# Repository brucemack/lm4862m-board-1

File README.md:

Overview
========

A KiCad schematic/PCB for a simple breakout board for the LM4862M 
audio amplifier.  Includes a connection for a volume control.

Schematic
=========

PCB
===

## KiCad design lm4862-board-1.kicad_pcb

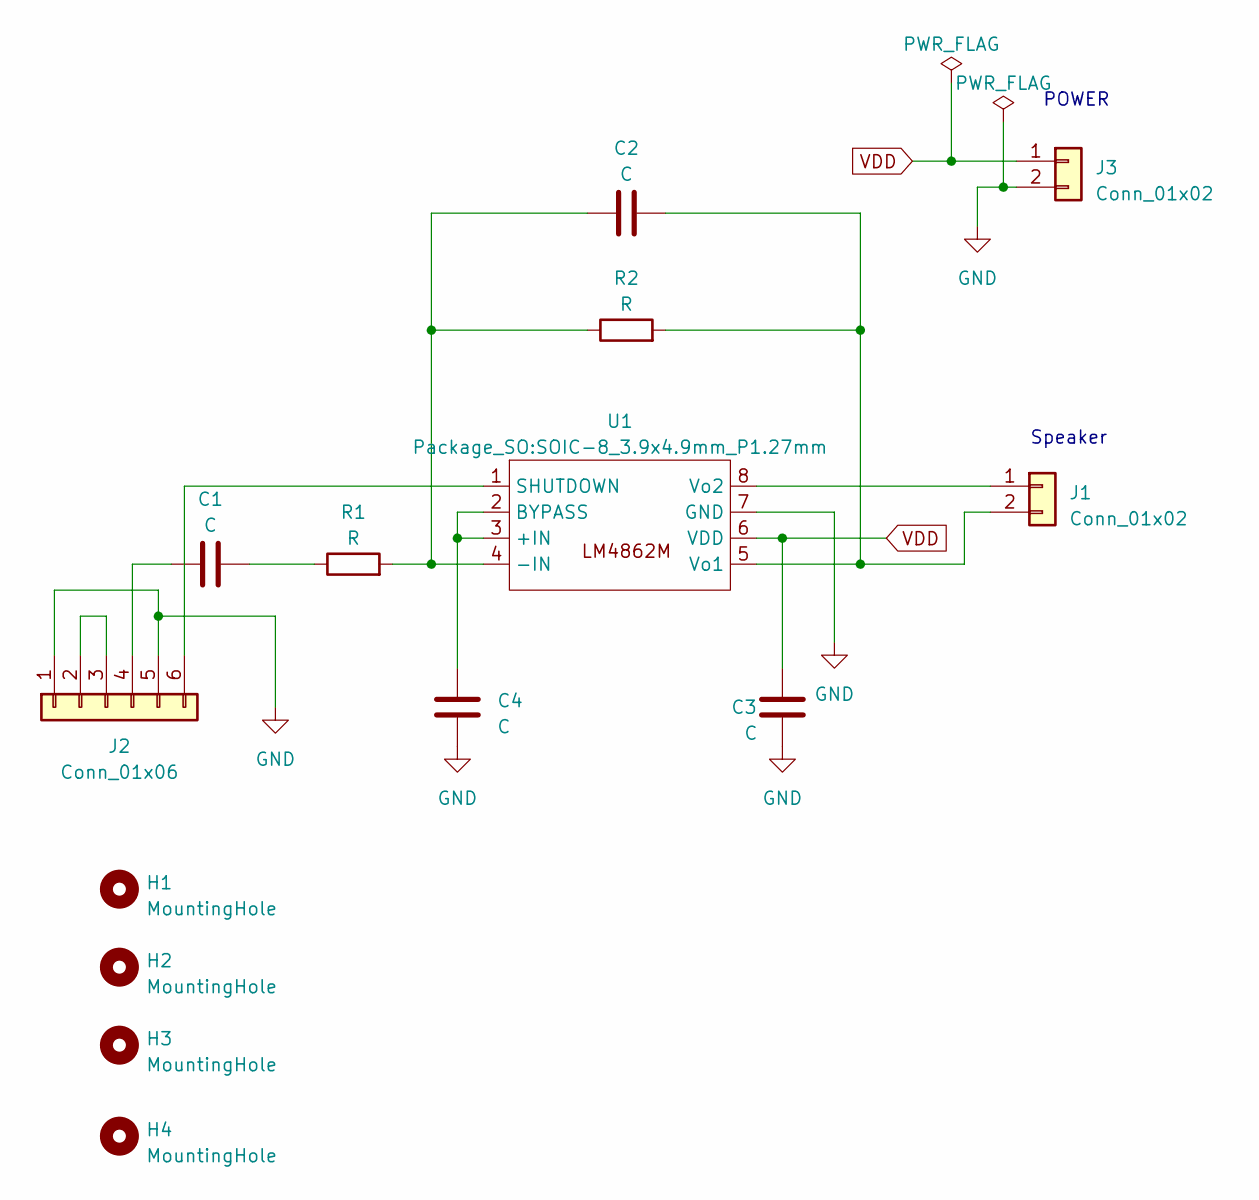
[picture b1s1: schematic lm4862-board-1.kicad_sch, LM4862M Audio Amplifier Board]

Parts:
C1, C2, C3, C4: C; C_0805_2012Metric_Pad1.18x1.45mm_HandSolder
H1, H2, H3, H4: MountingHole; MountingHole_4mm
J1, J3: Conn_01x02; PinHeader_1x02_P2.54mm_Vertical
J2: Conn_01x06; PinHeader_1x06_P2.54mm_Vertical
R1, R2: R; R_0805_2012Metric_Pad1.20x1.40mm_HandSolder
U1: SOIC-8_3.9x4.9mm_P1.27mm

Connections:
GND: C3.2, C4.2, J2.1, J2.5, J3.2, U1.7 (GND)
unnamed: C1.2, R1.1
unnamed: J1.1, U1.8 (Vo2)
unnamed: C2.1, J1.2, R2.2, U1.5 (Vo1)
unnamed: J2.2, J2.3
unnamed: C1.1, J2.4
unnamed: J2.6, U1.1 (SHUTDOWN)
unnamed: C4.1, U1.2 (BYPASS), U1.3 (+IN)
unnamed: C2.2, R1.2, R2.1, U1.4 (-IN)
VDD: C3.1, J3.1, U1.6 (VDD)

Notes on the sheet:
POWER
Speaker

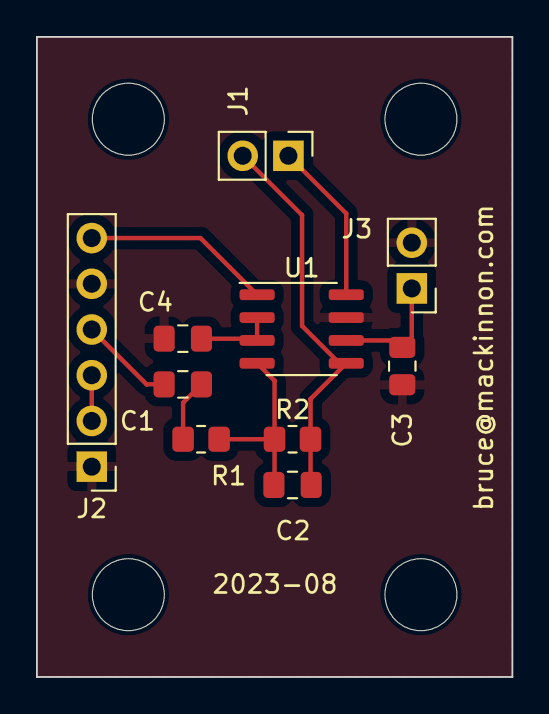
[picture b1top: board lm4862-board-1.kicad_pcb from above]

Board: 2 copper layers, 26.4 x 35.6 mm, 14 parts (0 on the bottom side), 10 nets.

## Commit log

2023-08-20 Updated docs
